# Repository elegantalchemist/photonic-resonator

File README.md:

Work in Progress

A self-blinking matrix of LEDS forming a 'supercomputer' which can calculate whatever you feel like. No computation, programming, coding or SOC or anything else needed to build it - entirely 'electromechanical' in function.

## Materials
* **Smoked perspex front/diffuser** - Frosted Grey S2 9T21 Perspex Acrylic 'Frost Stone Grey' or equivalent, has a 38% light transmission so fairly heavy diffusion. Cut to 315w x 111h - see dimensions in the CDR schematic file if you wanted to alter this size.
* **Brushed steel effect bottom plate** This is brushed steel effect laminated on black perspex, available from several brands often called 'Metalgraph' or 'Brushed stainless laminate' or similar. This can be either laser cut and engraved or CNC cut and engraved. My laser cut and engrave file is provided here in the CDR files folder in both Illustrator and CDR format.
* **Modular PCB** - all files included here for you to have this produced, I used JLCPCB including SMD assembly service for the resistors/diodes on the back. This PCB can be stacked if you so desire, it has output pads to make this super easy. Arranged for though-hole LEDs.
* **Baffle plate** to stop light leakage between LEDs - important and also allows different shapes. All the 3d printing files are enclosed here as STL files.
* **5mm Self-blinking through hole LEDs** These are 0.5Hz (one blink every 2 seconds) and are in red (625nm) and orange (600nm) with a forward voltage of 3-3.5V and 20mA power draw. The board has individual SMD resistors at 160 ohm to provide slightly less than operating specs to maximise lifespan, plus 3 diode options to supply even less voltage for less brightness. Ths both allows for selectable brightness as well as maximal lifespan.
* **LED Sourcing** I ordered in bulk from Alibaba see here - various colour options as well as different speeds but a hefty minimum order number [Alibaba JSTronic](https://www.alibaba.com/product-detail/Jstronic-0-5Hz-1-5Hz-2Hz_60724851074.html) but they can also be found in smaller quantities on eBay as self-blinking 5mm LEDs. It's absolutely critical they are self-blinking as this is the whole point of the project - zero code, zero computing, just slightly out of sync randomness turned into patterns. You can choose different speeds but higher speeds can be a bit chaotic.
* **Switches etc** Your choice as to what cool switches and dials you use. For this project I used the following  
[Momentary pushbutton - metal illuminated](https://thepihut.com/products/rugged-metal-pushbutton-with-red-led-ring) - 'reset' button on the front  
[Rotary selector - 4P3T](https://www.amazon.co.uk/dp/B0CZDS1686) - voltage selector to change brightness  
[Latching pushbutton](https://thepihut.com/products/16mm-illuminated-pushbutton-yellow-latching-on-off-switch) - side mounted on/off switch
* **Power Supply** 5V in is the designed power supply so this is a simple USB female socket mounted in the side or back of the case.
* **Case** No files here as I made it from wood - you could quite easily design and print something by 3D printing. My wood case is a simple long strip of wood with a 3mm channel cut into it for the perspex and 4 mitred corners to bring it into a box. Back plate is a piece of scrap ply cut to size placed in a rebate.

## Assembly
* Fairly straightforward - solder all your LEDs to your PCB taking care to respect polarity and that each LED is snug against the board and neatly centred - the baffles require the LEDS to have quite tight install tolerances. Test and ensure all working, they will happily self blink provided a 5V input to the input pads, and self blink with less brightness at each of the D1, D2, D3 in options.
* Add the control mechanisms - for simplicity in order your 5V should go through your on/off switch, reset button, rotary selector and the rotary selector output options be wired into whichever of the 3 pad 5v/D1/D2/D3 options you feel you like best. You could also add complexity by using the on/off pushbutton as a selctable toggle switch along with the rotary selector to choose a different set of output pins as well for example.
* -----to do - draw schematic----
* Assemble all the bits into a case of your choosing, done!

## Credits
Many thanks to MWWorks who posted their PCB and Baffle designs which have been modified and redesigned for this project  
[MWWorks Gallium Photonic Computer](https://github.com/MWWorks/gallium-photonic-computer)

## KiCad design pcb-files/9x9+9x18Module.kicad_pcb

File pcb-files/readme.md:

PCB Files in this folder, also as a zip download

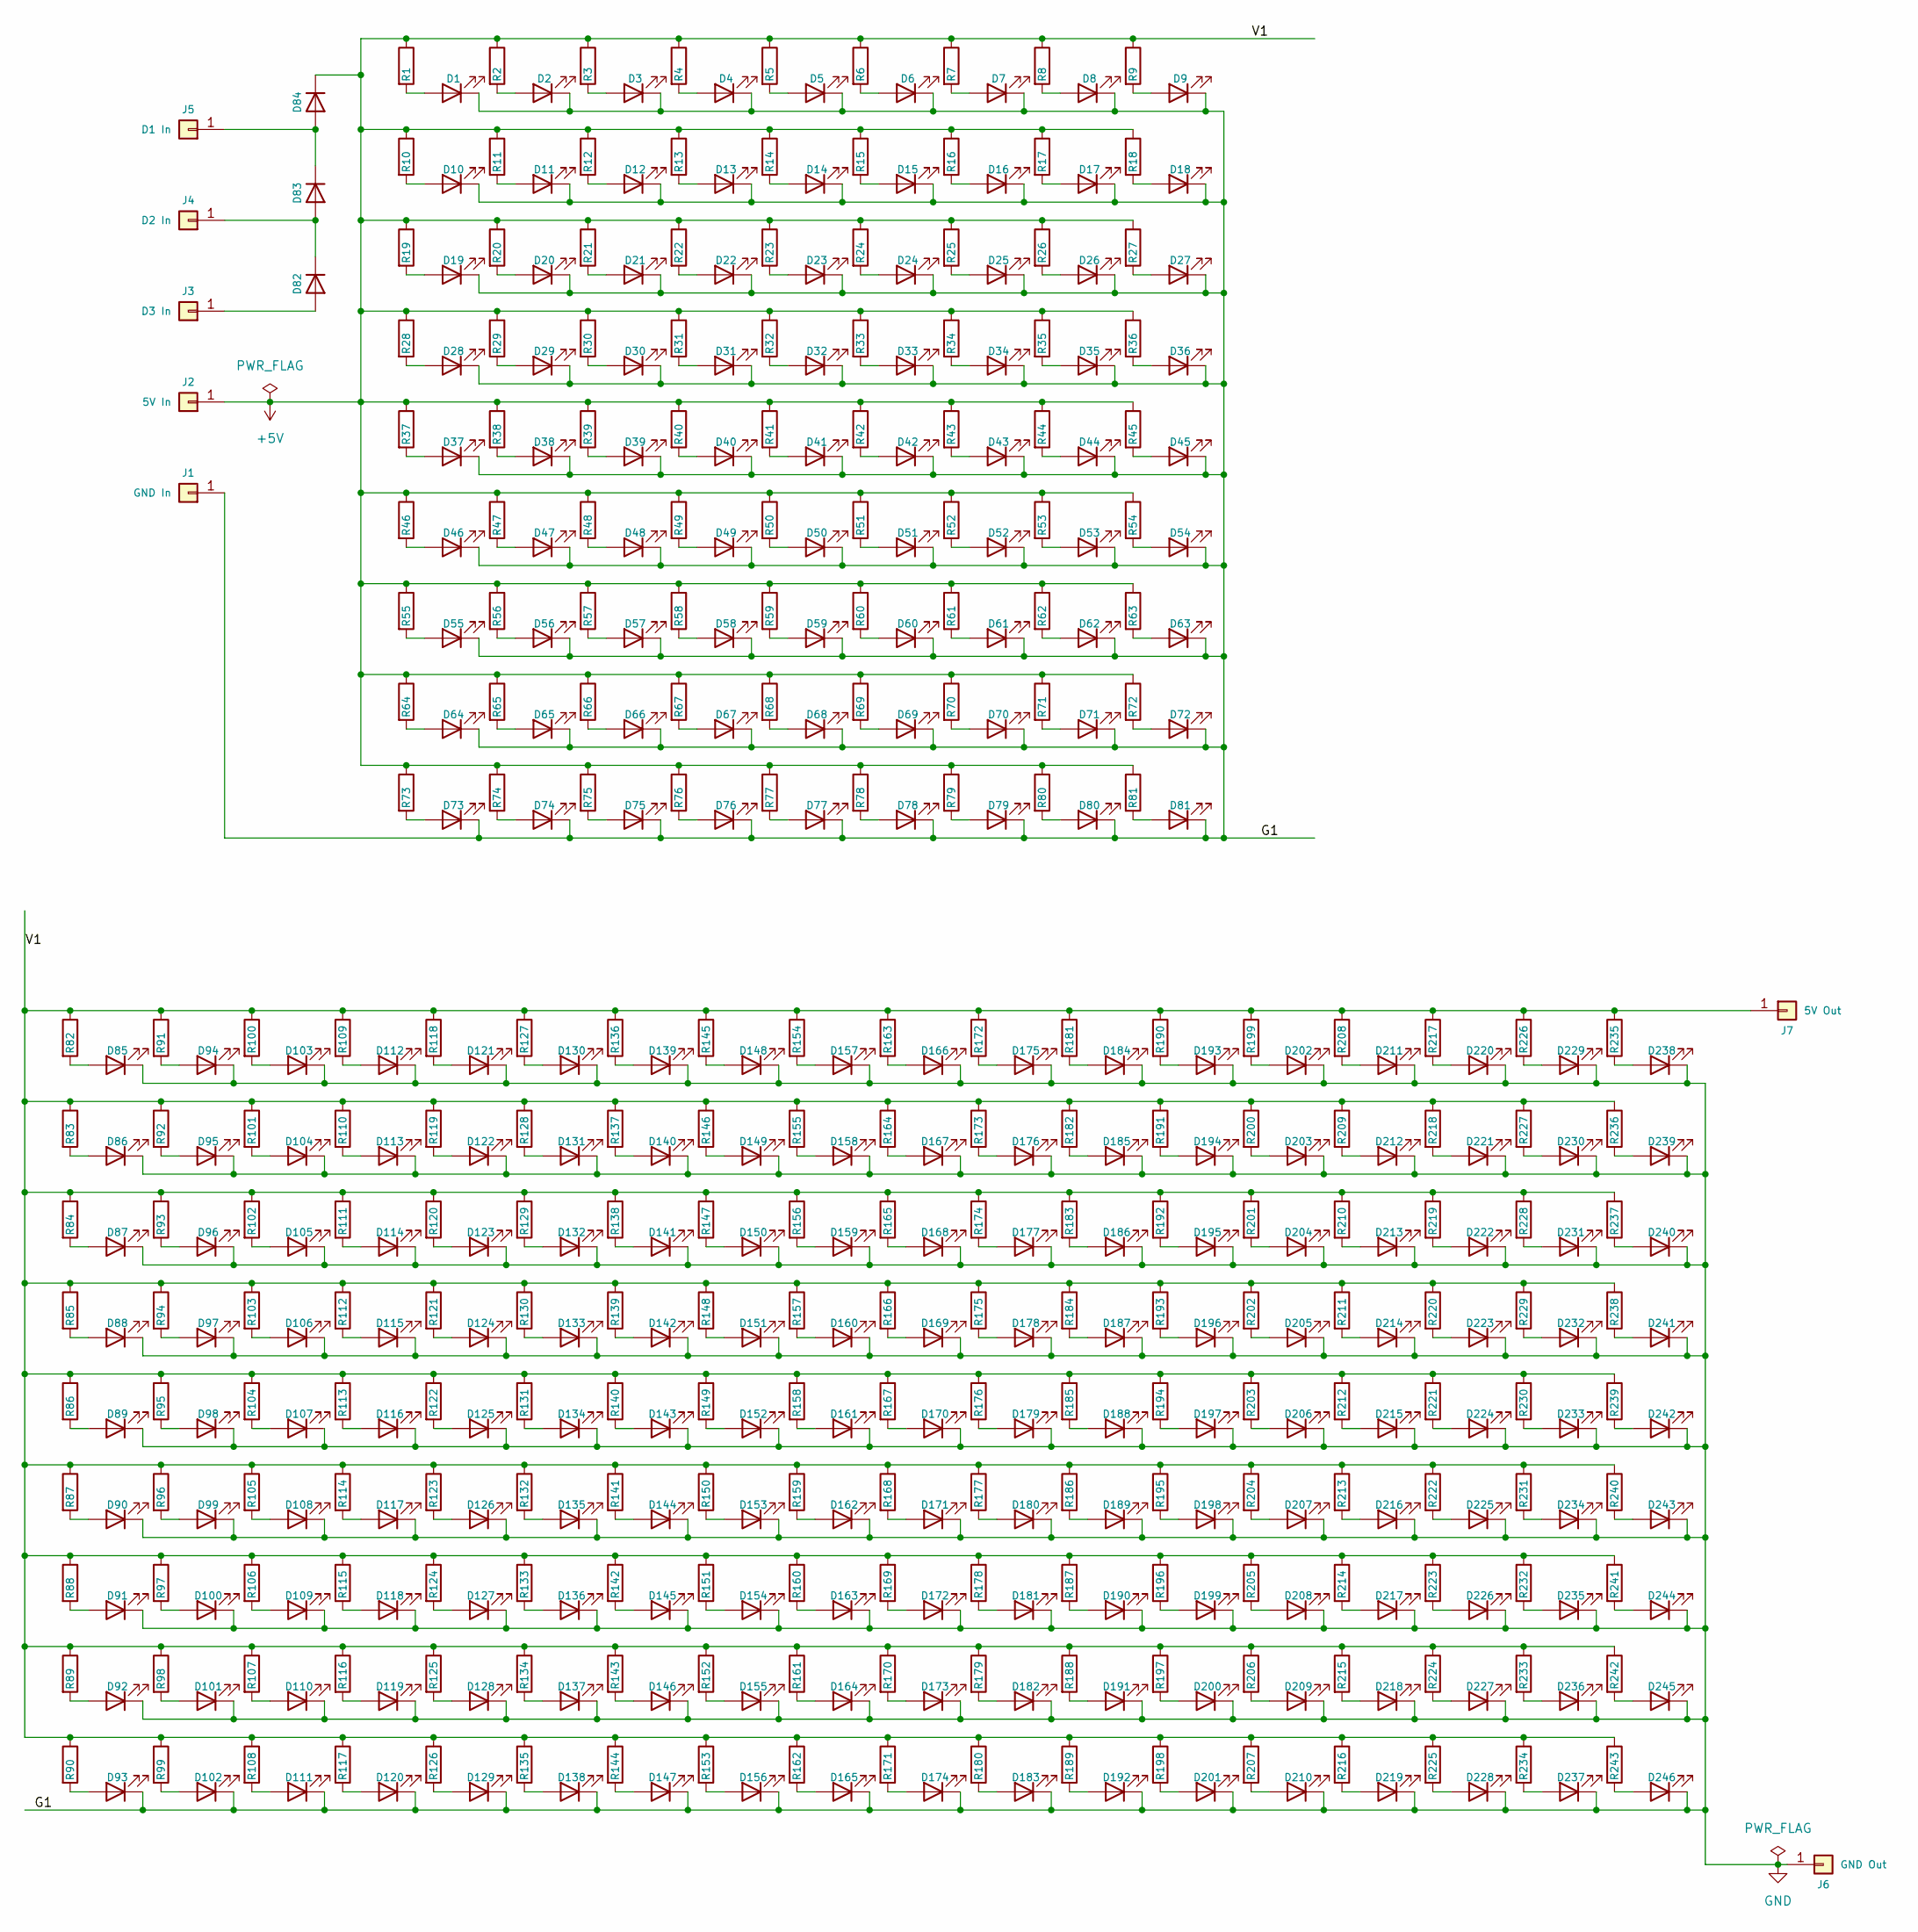
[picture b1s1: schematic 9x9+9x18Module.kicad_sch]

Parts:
D1, D2, D3, D4, D5, D6, D7, D8, D9, D10, D11, D12, D13, D14, D15, D16, D17, D18, D19, D20, D21, D22, D23, D24, D25, D26, D27, D28, D29, D30, D31, D32, D33, D34, D35, D36, D37, D38, D39, D40, D41, D42, D43, D44, D45, D46, D47, D48, D49, D50, D51, D52, D53, D54, D55, D56, D57, D58, D59, D60, D61, D62, D63, D64, D65, D66, D67, D68, D69, D70, D71, D72, D73, D74, D75, D76, D77, D78, D79, D80, D81, D85, D86, D87, D88, D89, D90, D91, D92, D93, D94, D95, D96, D97, D98, D99, D100, D101, D102, D103, D104, D105, D106, D107, D108, D109, D110, D111, D112, D113, D114, D115, D116, D117, D118, D119, D120, D121, D122, D123, D124, D125, D126, D127, D128, D129, D130, D131, D132, D133, D134, D135, D136, D137, D138, D139, D140, D141, D142, D143, D144, D145, D146, D147, D148, D149, D150, D151, D152, D153, D154, D155, D156, D157, D158, D159, D160, D161, D162, D163, D164, D165, D166, D167, D168, D169, D170, D171, D172, D173, D174, D175, D176, D177, D178, D179, D180, D181, D182, D183, D184, D185, D186, D187, D188, D189, D190, D191, D192, D193, D194, D195, D196, D197, D198, D199, D200, D201, D202, D203, D204, D205, D206, D207, D208, D209, D210, D211, D212, D213, D214, D215, D216, D217, D218, D219, D220, D221, D222, D223, D224, D225, D226, D227, D228, D229, D230, D231, D232, D233, D234, D235, D236, D237, D238, D239, D240, D241, D242, D243, D244, D245, D246: LED; LED_D5.0mm
D82, D83, D84: US2MA; D_SMA; LCSC C18905
J1: GND In; TestPoint_Pad_D4.0mm
J2: 5V In; TestPoint_Pad_D4.0mm
J3: D3 In; TestPoint_Pad_D4.0mm
J4: D2 In; TestPoint_Pad_D4.0mm
J5: D1 In; TestPoint_Pad_D4.0mm
J6: GND Out; TestPoint_Pad_D4.0mm
J7: 5V Out; TestPoint_Pad_D4.0mm
R1, R2, R3, R4, R5, R6, R7, R8, R9, R10, R11, R12, R13, R14, R15, R16, R17, R18, R19, R20, R21, R22, R23, R24, R25, R26, R27, R28, R29, R30, R31, R32, R33, R34, R35, R36, R37, R38, R39, R40, R41, R42, R43, R44, R45, R46, R47, R48, R49, R50, R51, R52, R53, R54, R55, R56, R57, R58, R59, R60, R61, R62, R63, R64, R65, R66, R67, R68, R69, R70, R71, R72, R73, R74, R75, R76, R77, R78, R79, R80, R81, R82, R83, R84, R85, R86, R87, R88, R89, R90, R91, R92, R93, R94, R95, R96, R97, R98, R99, R100, R101, R102, R103, R104, R105, R106, R107, R108, R109, R110, R111, R112, R113, R114, R115, R116, R117, R118, R119, R120, R121, R122, R123, R124, R125, R126, R127, R128, R129, R130, R131, R132, R133, R134, R135, R136, R137, R138, R139, R140, R141, R142, R143, R144, R145, R146, R147, R148, R149, R150, R151, R152, R153, R154, R155, R156, R157, R158, R159, R160, R161, R162, R163, R164, R165, R166, R167, R168, R169, R170, R171, R172, R173, R174, R175, R176, R177, R178, R179, R180, R181, R182, R183, R184, R185, R186, R187, R188, R189, R190, R191, R192, R193, R194, R195, R196, R197, R198, R199, R200, R201, R202, R203, R204, R205, R206, R207, R208, R209, R210, R211, R212, R213, R214, R215, R216, R217, R218, R219, R220, R221, R222, R223, R224, R225, R226, R227, R228, R229, R230, R231, R232, R233, R234, R235, R236, R237, R238, R239, R240, R241, R242, R243: 100R; R_0805_2012Metric; LCSC C17710

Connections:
+5V: D84.1 (K), J2.1, J7.1, R1.1, R2.1, R3.1, R4.1, R5.1, R6.1, R7.1, R8.1, R9.1, R10.1, R11.1, R12.1, R13.1, R14.1, R15.1, R16.1, R17.1, R18.1, R19.1, R20.1, R21.1, R22.1, R23.1, R24.1, R25.1, R26.1, R27.1, R28.1, R29.1, R30.1, R31.1, R32.1, R33.1, R34.1, R35.1, R36.1, R37.1, R38.1, R39.1, R40.1, R41.1, R42.1, R43.1, R44.1, R45.1, R46.1, R47.1, R48.1, R49.1, R50.1, R51.1, R52.1, R53.1, R54.1, R55.1, R56.1, R57.1, R58.1, R59.1, R60.1, R61.1, R62.1, R63.1, R64.1, R65.1, R66.1, R67.1, R68.1, R69.1, R70.1, R71.1, R72.1, R73.1, R74.1, R75.1, R76.1, R77.1, R78.1, R79.1, R80.1, R81.1, R82.1, R83.1, R84.1, R85.1, R86.1, R87.1, R88.1, R89.1, R90.1, R91.1, R92.1, R93.1, R94.1, R95.1, R96.1, R97.1, R98.1, R99.1, R100.1, R101.1, R102.1, R103.1, R104.1, R105.1, R106.1, R107.1, R108.1, R109.1, R110.1, R111.1, R112.1, R113.1, R114.1, R115.1, R116.1, R117.1, R118.1, R119.1, R120.1, R121.1, R122.1, R123.1, R124.1, R125.1, R126.1, R127.1, R128.1, R129.1, R130.1, R131.1, R132.1, R133.1, R134.1, R135.1, R136.1, R137.1, R138.1, R139.1, R140.1, R141.1, R142.1, R143.1, R144.1, R145.1, R146.1, R147.1, R148.1, R149.1, R150.1, R151.1, R152.1, R153.1, R154.1, R155.1, R156.1, R157.1, R158.1, R159.1, R160.1, R161.1, R162.1, R163.1, R164.1, R165.1, R166.1, R167.1, R168.1, R169.1, R170.1, R171.1, R172.1, R173.1, R174.1, R175.1, R176.1, R177.1, R178.1, R179.1, R180.1, R181.1, R182.1, R183.1, R184.1, R185.1, R186.1, R187.1, R188.1, R189.1, R190.1, R191.1, R192.1, R193.1, R194.1, R195.1, R196.1, R197.1, R198.1, R199.1, R200.1, R201.1, R202.1, R203.1, R204.1, R205.1, R206.1, R207.1, R208.1, R209.1, R210.1, R211.1, R212.1, R213.1, R214.1, R215.1, R216.1, R217.1, R218.1, R219.1, R220.1, R221.1, R222.1, R223.1, R224.1, R225.1, R226.1, R227.1, R228.1, R229.1, R230.1, R231.1, R232.1, R233.1, R234.1, R235.1, R236.1, R237.1, R238.1, R239.1, R240.1, R241.1, R242.1, R243.1
GND: D1.1 (K), D2.1 (K), D3.1 (K), D4.1 (K), D5.1 (K), D6.1 (K), D7.1 (K), D8.1 (K), D9.1 (K), D10.1 (K), D11.1 (K), D12.1 (K), D13.1 (K), D14.1 (K), D15.1 (K), D16.1 (K), D17.1 (K), D18.1 (K), D19.1 (K), D20.1 (K), D21.1 (K), D22.1 (K), D23.1 (K), D24.1 (K), D25.1 (K), D26.1 (K), D27.1 (K), D28.1 (K), D29.1 (K), D30.1 (K), D31.1 (K), D32.1 (K), D33.1 (K), D34.1 (K), D35.1 (K), D36.1 (K), D37.1 (K), D38.1 (K), D39.1 (K), D40.1 (K), D41.1 (K), D42.1 (K), D43.1 (K), D44.1 (K), D45.1 (K), D46.1 (K), D47.1 (K), D48.1 (K), D49.1 (K), D50.1 (K), D51.1 (K), D52.1 (K), D53.1 (K), D54.1 (K), D55.1 (K), D56.1 (K), D57.1 (K), D58.1 (K), D59.1 (K), D60.1 (K), D61.1 (K), D62.1 (K), D63.1 (K), D64.1 (K), D65.1 (K), D66.1 (K), D67.1 (K), D68.1 (K), D69.1 (K), D70.1 (K), D71.1 (K), D72.1 (K), D73.1 (K), D74.1 (K), D75.1 (K), D76.1 (K), D77.1 (K), D78.1 (K), D79.1 (K), D80.1 (K), D81.1 (K), D85.1 (K), D86.1 (K), D87.1 (K), D88.1 (K), D89.1 (K), D90.1 (K), D91.1 (K), D92.1 (K), D93.1 (K), D94.1 (K), D95.1 (K), D96.1 (K), D97.1 (K), D98.1 (K), D99.1 (K), D100.1 (K), D101.1 (K), D102.1 (K), D103.1 (K), D104.1 (K), D105.1 (K), D106.1 (K), D107.1 (K), D108.1 (K), D109.1 (K), D110.1 (K), D111.1 (K), D112.1 (K), D113.1 (K), D114.1 (K), D115.1 (K), D116.1 (K), D117.1 (K), D118.1 (K), D119.1 (K), D120.1 (K), D121.1 (K), D122.1 (K), D123.1 (K), D124.1 (K), D125.1 (K), D126.1 (K), D127.1 (K), D128.1 (K), D129.1 (K), D130.1 (K), D131.1 (K), D132.1 (K), D133.1 (K), D134.1 (K), D135.1 (K), D136.1 (K), D137.1 (K), D138.1 (K), D139.1 (K), D140.1 (K), D141.1 (K), D142.1 (K), D143.1 (K), D144.1 (K), D145.1 (K), D146.1 (K), D147.1 (K), D148.1 (K), D149.1 (K), D150.1 (K), D151.1 (K), D152.1 (K), D153.1 (K), D154.1 (K), D155.1 (K), D156.1 (K), D157.1 (K), D158.1 (K), D159.1 (K), D160.1 (K), D161.1 (K), D162.1 (K), D163.1 (K), D164.1 (K), D165.1 (K), D166.1 (K), D167.1 (K), D168.1 (K), D169.1 (K), D170.1 (K), D171.1 (K), D172.1 (K), D173.1 (K), D174.1 (K), D175.1 (K), D176.1 (K), D177.1 (K), D178.1 (K), D179.1 (K), D180.1 (K), D181.1 (K), D182.1 (K), D183.1 (K), D184.1 (K), D185.1 (K), D186.1 (K), D187.1 (K), D188.1 (K), D189.1 (K), D190.1 (K), D191.1 (K), D192.1 (K), D193.1 (K), D194.1 (K), D195.1 (K), D196.1 (K), D197.1 (K), D198.1 (K), D199.1 (K), D200.1 (K), D201.1 (K), D202.1 (K), D203.1 (K), D204.1 (K), D205.1 (K), D206.1 (K), D207.1 (K), D208.1 (K), D209.1 (K), D210.1 (K), D211.1 (K), D212.1 (K), D213.1 (K), D214.1 (K), D215.1 (K), D216.1 (K), D217.1 (K), D218.1 (K), D219.1 (K), D220.1 (K), D221.1 (K), D222.1 (K), D223.1 (K), D224.1 (K), D225.1 (K), D226.1 (K), D227.1 (K), D228.1 (K), D229.1 (K), D230.1 (K), D231.1 (K), D232.1 (K), D233.1 (K), D234.1 (K), D235.1 (K), D236.1 (K), D237.1 (K), D238.1 (K), D239.1 (K), D240.1 (K), D241.1 (K), D242.1 (K), D243.1 (K), D244.1 (K), D245.1 (K), D246.1 (K), J1.1, J6.1
unnamed: D1.2 (A), R1.2
unnamed: D2.2 (A), R2.2
unnamed: D3.2 (A), R3.2
unnamed: D4.2 (A), R4.2
unnamed: D5.2 (A), R5.2
unnamed: D6.2 (A), R6.2
unnamed: D7.2 (A), R7.2
unnamed: D8.2 (A), R8.2
unnamed: D9.2 (A), R9.2
unnamed: D10.2 (A), R10.2
unnamed: D11.2 (A), R11.2
unnamed: D12.2 (A), R12.2
unnamed: D13.2 (A), R13.2
unnamed: D14.2 (A), R14.2
unnamed: D15.2 (A), R15.2
unnamed: D16.2 (A), R16.2
unnamed: D17.2 (A), R17.2
unnamed: D18.2 (A), R18.2
unnamed: D19.2 (A), R19.2
unnamed: D20.2 (A), R20.2
unnamed: D21.2 (A), R21.2
unnamed: D22.2 (A), R22.2
unnamed: D23.2 (A), R23.2
unnamed: D24.2 (A), R24.2
unnamed: D25.2 (A), R25.2
unnamed: D26.2 (A), R26.2
unnamed: D27.2 (A), R27.2
unnamed: D28.2 (A), R28.2
unnamed: D29.2 (A), R29.2
unnamed: D30.2 (A), R30.2
unnamed: D31.2 (A), R31.2
unnamed: D32.2 (A), R32.2
unnamed: D33.2 (A), R33.2
unnamed: D34.2 (A), R34.2
unnamed: D35.2 (A), R35.2
unnamed: D36.2 (A), R36.2
unnamed: D37.2 (A), R37.2
unnamed: D38.2 (A), R38.2
unnamed: D39.2 (A), R39.2
unnamed: D40.2 (A), R40.2
unnamed: D41.2 (A), R41.2
unnamed: D42.2 (A), R42.2
unnamed: D43.2 (A), R43.2
unnamed: D44.2 (A), R44.2
unnamed: D45.2 (A), R45.2
unnamed: D46.2 (A), R46.2
unnamed: D47.2 (A), R47.2
unnamed: D48.2 (A), R48.2
unnamed: D49.2 (A), R49.2
unnamed: D50.2 (A), R50.2
unnamed: D51.2 (A), R51.2
unnamed: D52.2 (A), R52.2
unnamed: D53.2 (A), R53.2
unnamed: D54.2 (A), R54.2
unnamed: D55.2 (A), R55.2
unnamed: D56.2 (A), R56.2
unnamed: D57.2 (A), R57.2
unnamed: D58.2 (A), R58.2
unnamed: D59.2 (A), R59.2
unnamed: D60.2 (A), R60.2
unnamed: D61.2 (A), R61.2
unnamed: D62.2 (A), R62.2
unnamed: D63.2 (A), R63.2
unnamed: D64.2 (A), R64.2
unnamed: D65.2 (A), R65.2
unnamed: D66.2 (A), R66.2
unnamed: D67.2 (A), R67.2
unnamed: D68.2 (A), R68.2
unnamed: D69.2 (A), R69.2
unnamed: D70.2 (A), R70.2
unnamed: D71.2 (A), R71.2
unnamed: D72.2 (A), R72.2
unnamed: D73.2 (A), R73.2
unnamed: D74.2 (A), R74.2
unnamed: D75.2 (A), R75.2
unnamed: D76.2 (A), R76.2
unnamed: D77.2 (A), R77.2
unnamed: D78.2 (A), R78.2
unnamed: D79.2 (A), R79.2
unnamed: D80.2 (A), R80.2
unnamed: D81.2 (A), R81.2
unnamed: D82.2 (A), J3.1
unnamed: D82.1 (K), D83.2 (A), J4.1
unnamed: D83.1 (K), D84.2 (A), J5.1
unnamed: D85.2 (A), R82.2
unnamed: D86.2 (A), R83.2
unnamed: D87.2 (A), R84.2
unnamed: D88.2 (A), R85.2
unnamed: D89.2 (A), R86.2
unnamed: D90.2 (A), R87.2
unnamed: D91.2 (A), R88.2
unnamed: D92.2 (A), R89.2
unnamed: D93.2 (A), R90.2
unnamed: D94.2 (A), R91.2
unnamed: D95.2 (A), R92.2
unnamed: D96.2 (A), R93.2
unnamed: D97.2 (A), R94.2
unnamed: D98.2 (A), R95.2
unnamed: D99.2 (A), R96.2
unnamed: D100.2 (A), R97.2
unnamed: D101.2 (A), R98.2
unnamed: D102.2 (A), R99.2
unnamed: D103.2 (A), R100.2
unnamed: D104.2 (A), R101.2
unnamed: D105.2 (A), R102.2
unnamed: D106.2 (A), R103.2
unnamed: D107.2 (A), R104.2
unnamed: D108.2 (A), R105.2
unnamed: D109.2 (A), R106.2
unnamed: D110.2 (A), R107.2
unnamed: D111.2 (A), R108.2
unnamed: D112.2 (A), R109.2
unnamed: D113.2 (A), R110.2
unnamed: D114.2 (A), R111.2
unnamed: D115.2 (A), R112.2
unnamed: D116.2 (A), R113.2
unnamed: D117.2 (A), R114.2
unnamed: D118.2 (A), R115.2
unnamed: D119.2 (A), R116.2
unnamed: D120.2 (A), R117.2
unnamed: D121.2 (A), R118.2
unnamed: D122.2 (A), R119.2
unnamed: D123.2 (A), R120.2
unnamed: D124.2 (A), R121.2
unnamed: D125.2 (A), R122.2
unnamed: D126.2 (A), R123.2
unnamed: D127.2 (A), R124.2
unnamed: D128.2 (A), R125.2
unnamed: D129.2 (A), R126.2
unnamed: D130.2 (A), R127.2
unnamed: D131.2 (A), R128.2
unnamed: D132.2 (A), R129.2
unnamed: D133.2 (A), R130.2
unnamed: D134.2 (A), R131.2
unnamed: D135.2 (A), R132.2
unnamed: D136.2 (A), R133.2
unnamed: D137.2 (A), R134.2
unnamed: D138.2 (A), R135.2
unnamed: D139.2 (A), R136.2
unnamed: D140.2 (A), R137.2
unnamed: D141.2 (A), R138.2
unnamed: D142.2 (A), R139.2
unnamed: D143.2 (A), R140.2
unnamed: D144.2 (A), R141.2
unnamed: D145.2 (A), R142.2
unnamed: D146.2 (A), R143.2
unnamed: D147.2 (A), R144.2
unnamed: D148.2 (A), R145.2
unnamed: D149.2 (A), R146.2
unnamed: D150.2 (A), R147.2
unnamed: D151.2 (A), R148.2
unnamed: D152.2 (A), R149.2
unnamed: D153.2 (A), R150.2
unnamed: D154.2 (A), R151.2
unnamed: D155.2 (A), R152.2
unnamed: D156.2 (A), R153.2
unnamed: D157.2 (A), R154.2
unnamed: D158.2 (A), R155.2
unnamed: D159.2 (A), R156.2
unnamed: D160.2 (A), R157.2
unnamed: D161.2 (A), R158.2
unnamed: D162.2 (A), R159.2
unnamed: D163.2 (A), R160.2
unnamed: D164.2 (A), R161.2
unnamed: D165.2 (A), R162.2
unnamed: D166.2 (A), R163.2
unnamed: D167.2 (A), R164.2
unnamed: D168.2 (A), R165.2
unnamed: D169.2 (A), R166.2
unnamed: D170.2 (A), R167.2
unnamed: D171.2 (A), R168.2
unnamed: D172.2 (A), R169.2
unnamed: D173.2 (A), R170.2
unnamed: D174.2 (A), R171.2
unnamed: D175.2 (A), R172.2
unnamed: D176.2 (A), R173.2
unnamed: D177.2 (A), R174.2
unnamed: D178.2 (A), R175.2
unnamed: D179.2 (A), R176.2
unnamed: D180.2 (A), R177.2
unnamed: D181.2 (A), R178.2
unnamed: D182.2 (A), R179.2
unnamed: D183.2 (A), R180.2
unnamed: D184.2 (A), R181.2
unnamed: D185.2 (A), R182.2
unnamed: D186.2 (A), R183.2
unnamed: D187.2 (A), R184.2
unnamed: D188.2 (A), R185.2
unnamed: D189.2 (A), R186.2
unnamed: D190.2 (A), R187.2
unnamed: D191.2 (A), R188.2
unnamed: D192.2 (A), R189.2
unnamed: D193.2 (A), R190.2
unnamed: D194.2 (A), R191.2
unnamed: D195.2 (A), R192.2
unnamed: D196.2 (A), R193.2
unnamed: D197.2 (A), R194.2
unnamed: D198.2 (A), R195.2
unnamed: D199.2 (A), R196.2
unnamed: D200.2 (A), R197.2
unnamed: D201.2 (A), R198.2
unnamed: D202.2 (A), R199.2
unnamed: D203.2 (A), R200.2
unnamed: D204.2 (A), R201.2
unnamed: D205.2 (A), R202.2
unnamed: D206.2 (A), R203.2
unnamed: D207.2 (A), R204.2
unnamed: D208.2 (A), R205.2
unnamed: D209.2 (A), R206.2
unnamed: D210.2 (A), R207.2
unnamed: D211.2 (A), R208.2
unnamed: D212.2 (A), R209.2
unnamed: D213.2 (A), R210.2
unnamed: D214.2 (A), R211.2
unnamed: D215.2 (A), R212.2
unnamed: D216.2 (A), R213.2
unnamed: D217.2 (A), R214.2
unnamed: D218.2 (A), R215.2
unnamed: D219.2 (A), R216.2
unnamed: D220.2 (A), R217.2
unnamed: D221.2 (A), R218.2
unnamed: D222.2 (A), R219.2
unnamed: D223.2 (A), R220.2
unnamed: D224.2 (A), R221.2
unnamed: D225.2 (A), R222.2
unnamed: D226.2 (A), R223.2
unnamed: D227.2 (A), R224.2
unnamed: D228.2 (A), R225.2
unnamed: D229.2 (A), R226.2
unnamed: D230.2 (A), R227.2
unnamed: D231.2 (A), R228.2
unnamed: D232.2 (A), R229.2
unnamed: D233.2 (A), R230.2
unnamed: D234.2 (A), R231.2
unnamed: D235.2 (A), R232.2
unnamed: D236.2 (A), R233.2
unnamed: D237.2 (A), R234.2
unnamed: D238.2 (A), R235.2
unnamed: D239.2 (A), R236.2
unnamed: D240.2 (A), R237.2
unnamed: D241.2 (A), R238.2
unnamed: D242.2 (A), R239.2
unnamed: D243.2 (A), R240.2
unnamed: D244.2 (A), R241.2
unnamed: D245.2 (A), R242.2
unnamed: D246.2 (A), R243.2

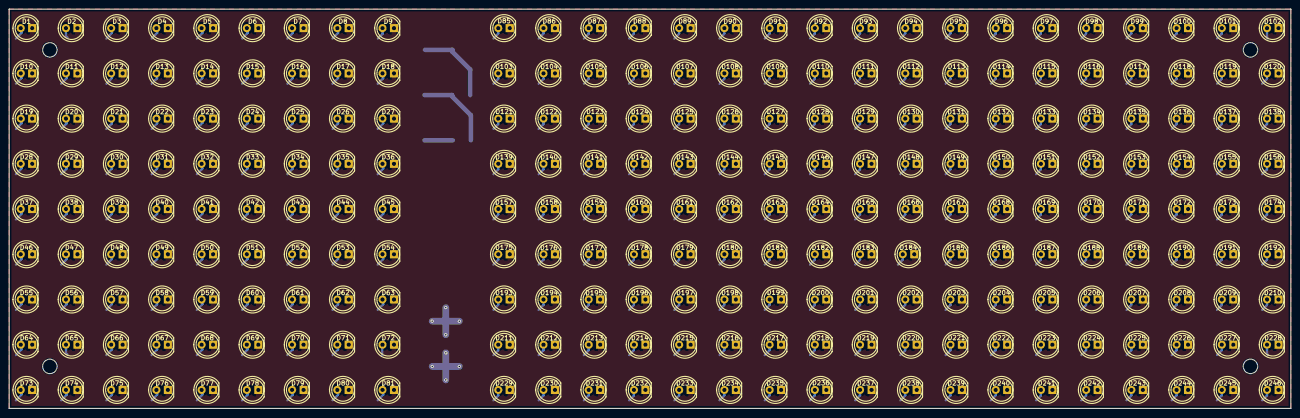
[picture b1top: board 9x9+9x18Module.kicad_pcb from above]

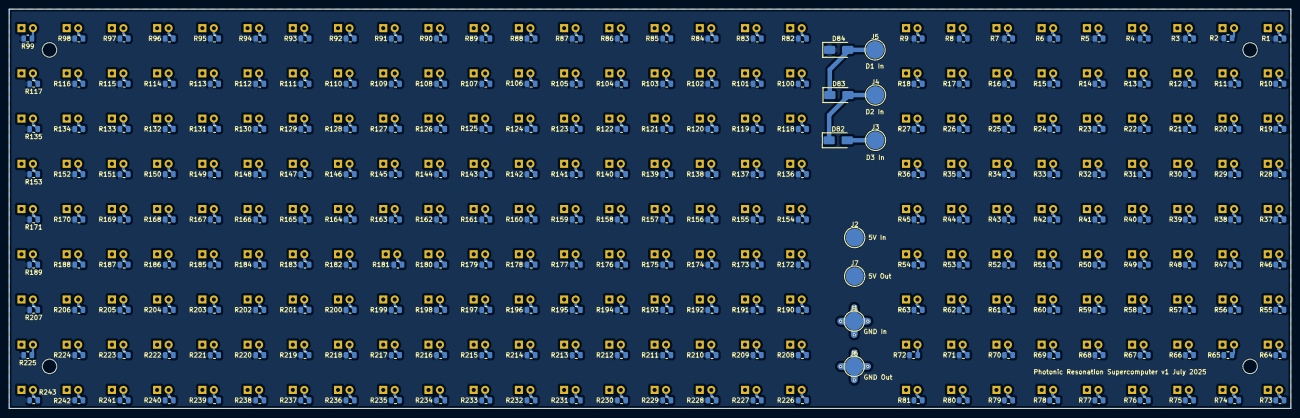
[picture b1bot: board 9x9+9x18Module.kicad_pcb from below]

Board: 2 copper layers, 283.4 x 88.3 mm, 496 parts (253 on the bottom side), 248 nets.

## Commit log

2025-08-06 Create cdr_files
